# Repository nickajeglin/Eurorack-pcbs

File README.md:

# Eurorack-pcbs
A collection of easy to solder DIY eurorack PCB's. All IC's are SOIC or DIP, passives are 1206 or THT for ease of soldering. There are also faceplate drill templates and graphics that can be used for toner transfer. Some utility modules are set up as 1u pcb's so you can mix and match 3 at a time in a standard 3u panel with only 1 eurorack power connector needed. 

> [!IMPORTANT]
> # 2025 update
> I've been away from this for some time, but the modules are still good subject to the notes below. I've been trying to give away spare PCB's at events etc. If you have one of those please be sure to check the issues pages for some minor rework requirements depending on your PCB version. I don't have most socials, so if you need help you can try to dm me on reddit or maybe post an issue here. As a side note, I lost huge amount of data during a work move. That means anything mentioned below that isn't uploaded is gone :'( it's especially disappointing for the VCS, as it's one of my favorite modules. You can still find it with it's original designer [here.](https://github.com/kassu/kassutronics/tree/master/documentation/Slope)
> 
> I don't think that I will go back and recreate what is gone. Losing so much work is disappointing and disheartening, but truthfully it's time to move on. Back in 2019, unchecked mental illness helped me maintain the sort of work output that is unhealthy in the long run. As I've gotten a handle on that I've needed to slow down on some hobbies, and this is one of them.     
> This will probably be my last commit on this repository. I hope that these PCB's will help someone make some kickass music.
> 
> *Nick, 2025-01-03*
>
> **P.S.** One item thankfully spared from the data loss was my semi-artistic layout of the 1972 "surf synthesizer" detailed midway through [this article.](https://www.preservationsound.com/2011/01/music-synthesizers-in-popular-electronics-1972/) The original article is included in the build docs folder and has some tips on adjusting the circuit properly. Enjoy :D
> 
> 

# PCB status summary:
**VCA:** ready to build, digikey bom provided

**VCO:** ready to build, digikey bom provided, minor rework needed for V1.0, V2.0 ok. 

**Mult:** Super easy first DIY project no surface mount parts. Ready to build, see interactive BOM for parts list, there's only like 3.

**Mixer:**
Update 2019-04-28: prototypes built. I reversed the supply rails on the TL072 in the kicad schematic lol. That means I need to flip the power header, and change some silk around. Let me know if you want V1.0 and I'll email it to you

Update 2019-05-15: prototypes are working. I gotta put the revision together to fix the reversed supply issue, but my job is kicking my ass right now, so it could be a month or more before I get around to it. If you're desperate for a cheap mixer, shoot me an email and I'll send you V1 files. Rework of V1 consists of flipping the euro power header and bypass caps 180 deg from the silk on the PCB layout. 

**~1u LFO:** ready to build, minor rework needed for V1.0 !!There's a stalling issue at low frequency I can't figure out!! see the issues page for details You probably don't want to use this. I'm too dumb to figure out the stalling issue, so these are only good for 50hz-->audio rate modulation. I did a layout of David Haillant's LFO with SMD components, but I haven't asked permission to share the files yet. Watch this space. 

**3->1 averager/mixer:** Prototypes tested and working. Doing cleanup for release (bypass caps intefere with plugging the damn thing in). Let me know if you want V1.0 and I'll email it to you. 

**1u 1->3 mult:** ~~schematic finished, pcb layout in queue~~ I'll probably never get around to finishing this one, since I already did the BiggerBetter THT mult above. If you want a 1u mult bad let me know and I'll finish it up sometime while I'm supposed to be working :D. But really, if you want a 1u mult that bad you can probably figure it out yourself from muffwiggler forum posts. 

**VCF:** low priority for now--> maybe I'll make a tranisitor ladder VCF. 

**VCS:** PCB's are in, most of the pots are reversed as well as all of the SOT23 transistors. Otherwise it **kicks ass**. I haven't asked the kassutronics guy permission to post this one yet, but I'll get around to it once I've got a solid rework strategy for V1.0.

**LOGIC**: Ready to build. 

# General Notes

**How expensive is this?:** Common knowledge says that DIY is usually not cheaper than buying retail because economy of scale, educational mistakes etc. But look, eurorack modules are boutique shit, so in this case you'd be hard pressed to build this stuff for more than retail cost. Here's some fast numbers off the top of my head: BOM's for each module are between 20 and 50 USD with shipping. A run of 3-10 PCB's costs between 15 and 50 USD with shipping depending on fab house. So we'll call that 35-100 USD per module. If you're just starting out, plan to make lots of mistakes and double it. I've finished about 24 modules since January 2019 and spent about $1500 for an average of $62 per module. Now I have to sleep with one eye open so my wife doesn't kill me for life insurance money, but *learning is priceless* so at least there's that I guess.  

**IMPORTANT:** Do not plug these in backwards. First of all, (most) don't have any reverse polarity protection so it will probably kill the module. Second of all, I have no idea (and can't be responsible for) what will happen to the rest of the modules in your system if/when you do upend the power rails. Maybe I'll get around to adding rpp eventually, but for now I'm living dangerously by relying on shrouded headers. 

Most of these are not my circuit designs. I simply put them in kicad and did PCB layout for eurorack format. I'm a mechanical engineer, not an electrical one, so there may be minor (major lol) mistakes or violations of standard practice. I have tested all for functionality though. I can provide very limited support via email, but when it comes to troubleshooting, you're likely on your own. 

**SMD components**
All the passives on these are 1206 size components. As long as you have a [cheapo temperature controlled soldering iron](https://www.amazon.com/Weller-WLC100-40-Watt-Soldering-Station/dp/B000AS28UC/ref=sr_1_3?keywords=weller+soldering+station&qid=1558398140&s=hi&sr=1-3), it'll be no problem for you. After a little practice, you'll find them easier than through hole components. 

I know I said everything is 1206 size above, but I recently (04/2019) started using 0805 size parts. If you can handle 1206, I swear to god you can do 0805. They're basically the same width, so gripping them with tweezers is just as easy, but they're just a little shorter which makes laying out the PCB's much easier for me. Look at the ibom (interactive bom) files in each folder for the latest parts. I generate those straight from the latest PCB layouts before I upload, so they're guaranteed to have the correct part format. Mouser/digikey BOM's are more like 95% correct because I'm lazy. 

**Pots/Jacks/Switches**

Pots and jacks aren't included in any digikey or mouser carts. You want these ones if you're in the US: 

https://modularaddict.com/parts/synth-diy-parts/9mm-potentiometers

https://modularaddict.com/parts/jacks/pj301m12-jacks

Or similar from Thonk if you're in Europe. You can buy [several hundred jacks](https://www.aliexpress.com/item/Original-new-100-headset-socket-PJ-301M-3-5MM-audio-and-video-socket-measuring-90-degree/32919567094.html?spm=a2g0s.9042311.0.0.50554c4d2D22No) direct from China like I did, but you'll feel like a terrible person for not supporting your local diy suppliers, and the quality is *noticeably worse* than the ones from thonk or modular addict.    

Good switches can be hard to find. I love taiway switches from these people: 

https://lovemyswitches.com/categories/switches/toggle-switches/mini-toggle-switches.html

I have no affiliation with them, but they have switches with adorable little stubby levers, and I'll pay a premium for that shit any day. ~PCB's will accomodate "PCB mount" or "solder lug" style.~ Get PCB mount style for the moment. The current (2/2019) toggle switch footprint through holes are slightly narrow, so solder lug style switches require a little sand paper-ing of the terminals to fit.  

Faceplates: 2mm aluminum works perfectly. Regular drill bits will work, and you can cut it with woodworking tools if you're super careful. If you can't get ahold of that, go to a hobby or art store and get some 1/8" aircraft birch ply. It's thin but strong. I have been using toner transfer to print graphics and labelling onto the panels. It works for aluminum or wood and results in a distressed look that I kinda like. You can find a tutorial at instructables (https://www.instructables.com/id/Transfer-PHOTOS-to-METAL/) but here's the bullet points: 

1) Buy *water* based poly from the wood finish section of a hardware store. Paint a thin layer on the faceplate. 

2) Print out your design on a laser printer in reverse and stick it on the *wet* poly. 

3) Let it dry. I stick it in a warm oven to speed up the process.

4) Wet the paper, and gently rub it off. You don't need to get it all in 1 shot. You should repeat the drying and wetting/rubbing cycle 2 or 3 times to get the paper off without removing too much toner.

5) Hit it with another layer of poly for protection. 

**PCB fab houses**
I really like Aisler, but they are kind of expensive and shipping takes 2 weeks to the US (as of 5/2019 they now have US production, I haven't tried it yet though). They can definetly handle all of the features in these PCB's. I have also used oshpark with good results. JLCPCB is a cheaper option, even with 3 day DHL shipping to the US. All three can handle the plated slots for the jack and switch footprints with no problem.  

# Dual log/lin VCA: 

Design: Ray Wilson (please visit http://musicfromouterspace.com/)

Design alterations: None

Tested working 2019-02

Required kludges: The screw holes on the drill template are in a nonstandard spot. Adjust accordingly if you care

Notes: This one is super easy and goes together in less than an hour. It's a 2 board pannelized design. Make sure your PCB fab house can handle internal slots for the switch footprint and pannelization. (oshpark and aisler did it without issue.) I may revise this to a one board design in the future to reduce PCB costs. 

# VCO: 

Design: Ray Wilson (please visit http://musicfromouterspace.com/)

Design alterations: None

Tested working 2019-02

Required kludges: 

V2.0: Eurorack pwr connector interferes with pot feet on front of board. Simply bend one of the pot feet out of the way so it doesn't       contact the -12V side of the pwr connector. This is unlikely to be fixed in the near future unless someone else wants to reroute around a new power connector location. 

~V1.0 outer potentiometer leads for RV1 and RV2 are reversed and need to be jumpered (X style) to the correct holes.~

~Silk showing polarity for C12 is reversed (+ side of C12 should be at GND).~

~Eurorack pwr connector interferes with pot feet on front of board. Simply bend one of the pot feet out of the way so it doesn't       contact the -12V side of the pwr connector.~

Notes: U2 is really far away from U4. Use lots of flux and make sure that U1-U4 are soldered really nicely, otherwise it won't work. U5 has several pins that are not connected (specifically 2, 9, 10, 12, 15, 16). Depending on the PCB fab you use, they might instantly delaminate. Don't freak out, it's not a problem. There are some trimpot through holes that intersect jack footprints, so make sure you solder the jacks last, and clip the trimpot leads flush with the board.

# Mixer: 

Design: I guess this one is my own, but heavily influenced by information from Ray Wilson (please visit http://musicfromouterspace.com/)

Tested working 2019-02 (breadboard only)

Required kludges: N/A

Notes: PCB layout is incomplete as of 2019-02. This is a DC coupled (CV capable) 4 into 2 or 8 into 1 mixer. It's based off of Ray's mixers, but is simplified in that the switchable high gain channel has been replaced by a normal one. I have one of these running in my system right now that's just dead-bugged to the back of the faceplate. PCB layout is nearly completed, 

# Utility LFO (8K LFO)

(disregard the tht resistors, I ran out of smd ones, so I just bodged some on there.)

Design: Tim Parkhurst: Magic Smoke Electronics (http://electro-music.com/wiki/pmwiki.php?n=Schematics.MagicSmokeLFODesignByTimServo)

Design alterations: None

Tested working 2019-02

Required kludges: 
V2.0: Stalling may still be an issue at low freq. I'm working on that, see issue #14 if you can help. 

~V1.0:Coarse pot leads (RV11) are reversed. Swap them with jumpers. You also need to bend one of each pot support legs up under the pot to avoid the power chain pads. This circuit is stalling out at slow settings right now. See issue #14 if you can help explain why.~

Notes: This is shrunk down to be a 1u module. There are power chain jumpers so that you can put 3 of them in a standard 3u tall panel with only one eurorack pwr connector,  or you could build 1 and put it in a 1u tile. Pots are super close together, so the max knob size you can put on them is 13mm diameter. Davies 1900H clones from thonk or modular addict (or wherever) will be ok. 

# Buffered Mult

Design: Michael Barton (http://www.bartonmusicalcircuits.com) 

Design alterations: None

Tested working 2019-02

Required kludges: None

Notes: This one is actually THT. It's a super simple but emminently useful utility module. The only tip here is to make sure you place J10 and J13 before the power header if you use a shrouded connector. Otherwise the plastic shroud will cover up the tip connections. Provided with permission from Michael Barton. 
    
# Analog Logic

Design: ME!

tested working 2019-10-19

Notes: I'm excited about this one. It's my first real honest to god module design! 3 input attenuverting mixer that goes into analog AND, OR, an averager, and a comparator. You can use the attenuverters alone by plugging into the first row of jacks. This removes the corresponding signal from the logic section. Input 3 is normalled to +10V so it's attenuverter acts as the cutoff control if you don't plug anything into that jack.

NOTES FOR V1.0 PCB's: Prior to 2019-10-19. I mixed up diode footprints, so V1.0 boards have the miniscule SOD-523 footprint. V2.0 has SOD-323. Much more manageable.

V2.1 is current. I moved the potentiometers slightly based on feedback from a couple people. They're still on a diagonal, but a little further from the jacks and evenly spaced.

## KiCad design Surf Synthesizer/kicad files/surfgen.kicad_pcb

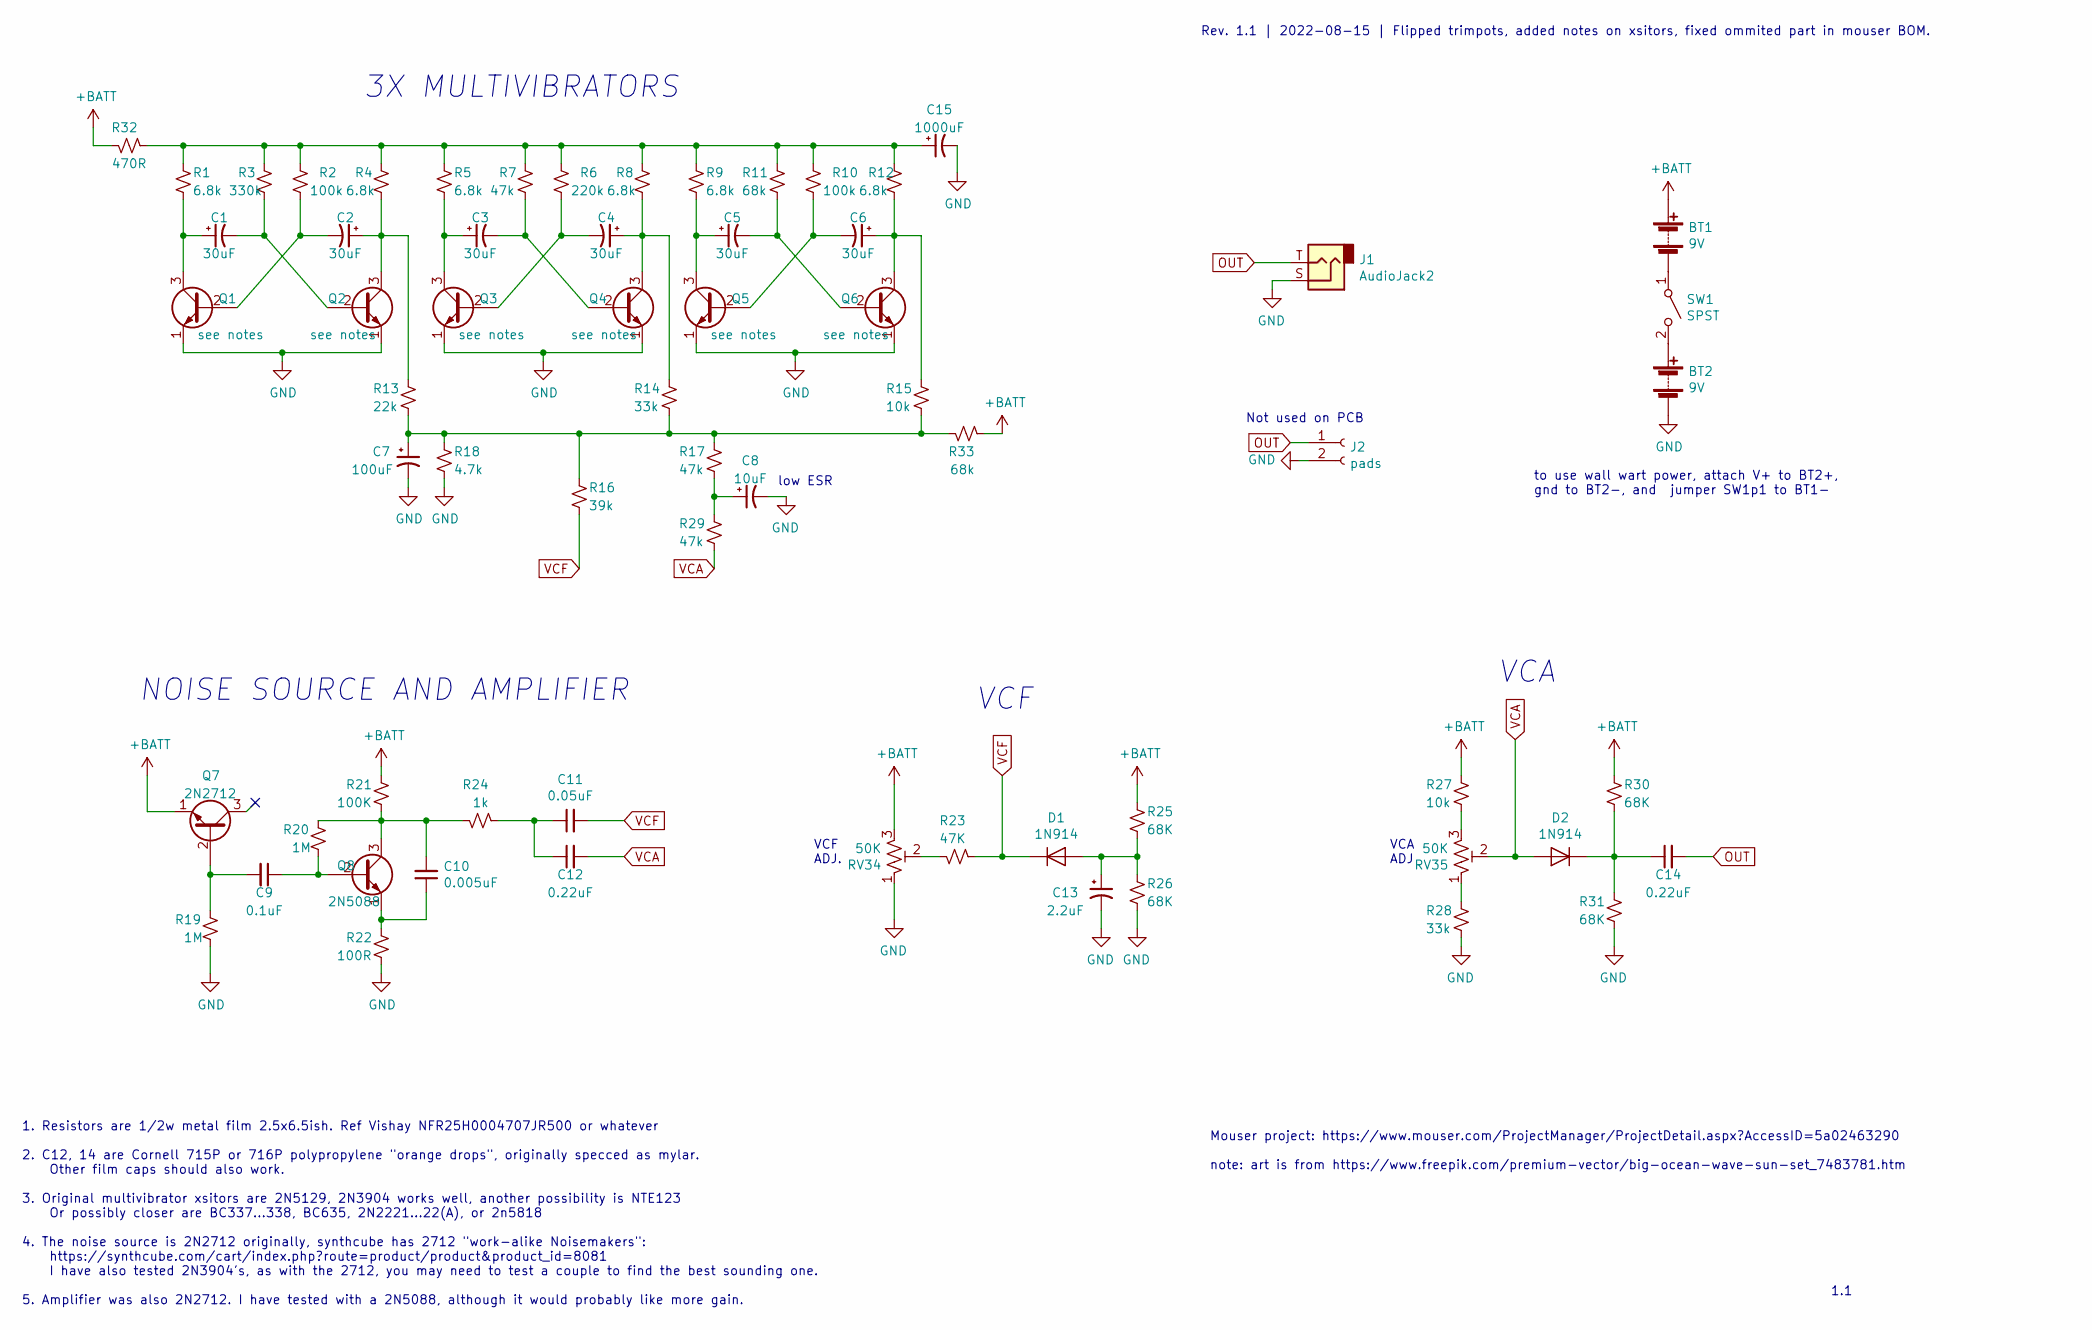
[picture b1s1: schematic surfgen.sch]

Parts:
BT1, BT2: 9V; TerminalBlock_Phoenix_MKDS-1,5-2-5.08_1x02_P5.08mm_Horizont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; Part Nr 651-1715721
C1, C2, C3, C4, C5, C6: 30uF; CP_Radial_D10.0mm_P5.00mm; Part Nr EGXF251ELL300MJ25S
C7: 100uF; CP_Radial_D10.0mm_P5.00mm; Part Nr MAL213631101E3
C8: 10uF; CP_Radial_D8.0mm_P5.00mm; Part Nr EEU-FR1H100B
C9: 0.1uF; C_Disc_D14.5mm_W5.0mm_P7.50mm; Part Nr S104Z93Z5VL83L0R
C10: 0.005uF; C_Disc_D11.0mm_W5.0mm_P7.50mm; Part Nr S502M39Z5UN63L6R
C11: 0.05uF; C_Disc_D16.0mm_W5.0mm_P10.00mm; Part Nr S503Z69Z5UL63L0R
C12, C14: 0.22uF; C_Rect_L28.0mm_W12.0mm_P22.50mm_MKS4; Part Nr 715P22452LD3
C13: 2.2uF; CP_Radial_D8.0mm_P5.00mm; Part Nr 860131274002
C15: 1000uF; C_Radial_D12.5mm_H20.0mm_P5.00mm; Part Nr EEU-FP1V102B
D1, D2: 1N914; D_DO-35_SOD27_P7.62mm_Horizontal; Part Nr 512-1N914
J1: AudioJack2; TerminalBlock_Phoenix_MKDS-1,5-2-5.08_1x02_P5.08mm_Horizont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; Part Nr 651-1715721
J2: pads; TerminalBlock_Phoenix_MKDS-1,5-2-5.08_1x02_P5.08mm_Horizont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; Part Nr 651-1715721
Q1, Q2, Q3, Q4, Q5, Q6: see notes; TO-92_HandSolder; Part Nr see notes
Q7: 2N2712; TO-92_HandSolder; Part Nr see notes
Q8: 2N5088; TO-92_HandSolder; Part Nr 610-2N5088
R1, R4, R5, R8, R9, R12: 6.8k; R_Axial_DIN0207_L6.3mm_D2.5mm_P10.16mm_Horizontal_refctr; Part Nr 71-CMF556K8000FKEB
R2, R10: 100k; R_Axial_DIN0207_L6.3mm_D2.5mm_P10.16mm_Horizontal_refctr; Part Nr 71-CMF55100K00BEEB
R3: 330k; R_Axial_DIN0207_L6.3mm_D2.5mm_P10.16mm_Horizontal_refctr; Part Nr 594-5053HD332K0F
R6: 220k; R_Axial_DIN0207_L6.3mm_D2.5mm_P10.16mm_Horizontal_refctr; Part Nr 71-CMF07220K00GKR6
R7, R17, R29: 47k; R_Axial_DIN0207_L6.3mm_D2.5mm_P10.16mm_Horizontal_refctr; Part Nr CMF5547K000FHEK
R11, R33: 68k; R_Axial_DIN0207_L6.3mm_D2.5mm_P10.16mm_Horizontal_refctr; Part Nr 594-SFR25H0006802JR5
R13: 22k; R_Axial_DIN0207_L6.3mm_D2.5mm_P10.16mm_Horizontal_refctr; Part Nr 594-5053HD22K10F
R14, R28: 33k; R_Axial_DIN0207_L6.3mm_D2.5mm_P10.16mm_Horizontal_refctr; Part Nr 594-SFR25H0003302JR5
R15, R27: 10k; R_Axial_DIN0207_L6.3mm_D2.5mm_P10.16mm_Horizontal_refctr; Part Nr 594-5053HD10K00F
R16: 39k; R_Axial_DIN0207_L6.3mm_D2.5mm_P10.16mm_Horizontal_refctr; Part Nr 594-5053HD39K20F
R18: 4.7k; R_Axial_DIN0207_L6.3mm_D2.5mm_P10.16mm_Horizontal_refctr; Part Nr 594-SFR25H0004701JR5
R19, R20: 1M; R_Axial_DIN0207_L6.3mm_D2.5mm_P10.16mm_Horizontal_refctr; Part Nr 594-SFR25H0001004JA5
R21: 100K; R_Axial_DIN0207_L6.3mm_D2.5mm_P10.16mm_Horizontal_refctr; Part Nr 71-CMF55100K00BEEB
R22: 100R; R_Axial_DIN0207_L6.3mm_D2.5mm_P10.16mm_Horizontal_refctr; Part Nr 594-5053HD100R0F
R23: 47K; R_Axial_DIN0207_L6.3mm_D2.5mm_P10.16mm_Horizontal_refctr; Part Nr CMF5547K000FHEK
R24: 1k; R_Axial_DIN0207_L6.3mm_D2.5mm_P10.16mm_Horizontal_refctr; Part Nr 594-5053HD1K000F
R25, R26, R30, R31: 68K; R_Axial_DIN0207_L6.3mm_D2.5mm_P10.16mm_Horizontal_refctr; Part Nr 594-SFR25H0006802JR5
R32: 470R; R_Axial_DIN0207_L6.3mm_D2.5mm_P10.16mm_Horizontal_refctr; Part Nr 594-SFR25H0004700FR5
RV34, RV35: 50K; Potentiometer_Bourns_3296Y_Vertical; Part Nr 3296Y-1-503LF
SW1: SPST; TerminalBlock_Phoenix_MKDS-1,5-2-5.08_1x02_P5.08mm_Horizont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; Part Nr 651-1715721

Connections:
+BATT: BT1.1 (+), Q7.1 (E), R21.1, R25.1, R27.1, R30.1, R32.1, R33.2, RV34.3
GND: BT2.2 (-), C7.2, C8.2, C13.2, C15.2, J1.S, J2.2, Q1.1 (E), Q2.1 (E), Q3.1 (E), Q4.1 (E), Q5.1 (E), Q6.1 (E), R18.2, R19.2, R22.2, R26.2, R28.2, R31.2, RV34.1
unnamed: BT1.2 (-), SW1.1 (A)
unnamed: BT2.1 (+), SW1.2 (B)
unnamed: C1.1, Q1.3 (C), R1.2
unnamed: C1.2, Q2.2 (B), R3.2
unnamed: C2.1, Q2.3 (C), R4.2, R13.1
unnamed: C2.2, Q1.2 (B), R2.2
unnamed: C3.1, Q3.3 (C), R5.2
unnamed: C3.2, Q4.2 (B), R7.2
unnamed: C4.1, Q4.3 (C), R8.2, R14.1
unnamed: C4.2, Q3.2 (B), R6.2
unnamed: C5.1, Q5.3 (C), R9.2
unnamed: C5.2, Q6.2 (B), R11.2
unnamed: C6.1, Q6.3 (C), R12.2, R15.1
unnamed: C6.2, Q5.2 (B), R10.2
unnamed: C7.1, R13.2, R14.2, R15.2, R16.1, R17.1, R18.1, R33.1
unnamed: C8.1, R17.2, R29.1
unnamed: C9.1, Q8.2 (B), R20.2
unnamed: C9.2, Q7.2 (B), R19.1
unnamed: C10.1, Q8.1 (E), R22.1
unnamed: C10.2, Q8.3 (C), R20.1, R21.2, R24.1
unnamed: C11.1, C12.1, R24.2
unnamed: C13.1, D1.2 (A), R25.2, R26.1
unnamed: C14.1, D2.1 (K), R30.2, R31.1
unnamed: C15.1, R1.1, R2.1, R3.1, R4.1, R5.1, R6.1, R7.1, R8.1, R9.1, R10.1, R11.1, R12.1, R32.2
unnamed: R23.1, RV34.2
unnamed: R27.2, RV35.3
unnamed: R28.1, RV35.1
OUT: C14.2, J1.T, J2.1
VCA: C12.2, D2.2 (A), R29.2, RV35.2
VCF: C11.2, D1.1 (K), R16.2, R23.2

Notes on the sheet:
3X MULTIVIBRATORS
NOISE SOURCE AND AMPLIFIER
VCF
VCA
low ESR
1. Resistors are 1/2w metal film 2.5x6.5ish. Ref Vishay NFR25H0004707JR500 or whatever 2. C12, 14 are Cornell 715P or 716P polypropylene "orange drops", originally specced as mylar. Other film caps should also work. 3. Original multivibrator xsitors are 2N5129, 2N3904 works well, another possibilit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
Mouser project: https://www.mouser.com/ProjectManager/ProjectDetail.aspx?AccessID=5a02463290 note: art is from https://www.freepik.com/premium-vector/big-ocean-wave-sun-set_7483781.htm
to use wall wart power, attach V+ to BT2+, gnd to BT2-, and jumper SW1p1 to BT1-
VCF ADJ.
VCA ADJ
Not used on PCB
Rev. 1.1 | 2022-08-15 | Flipped trimpots, added notes on xsitors, fixed ommited part in mouser BOM.
1.1

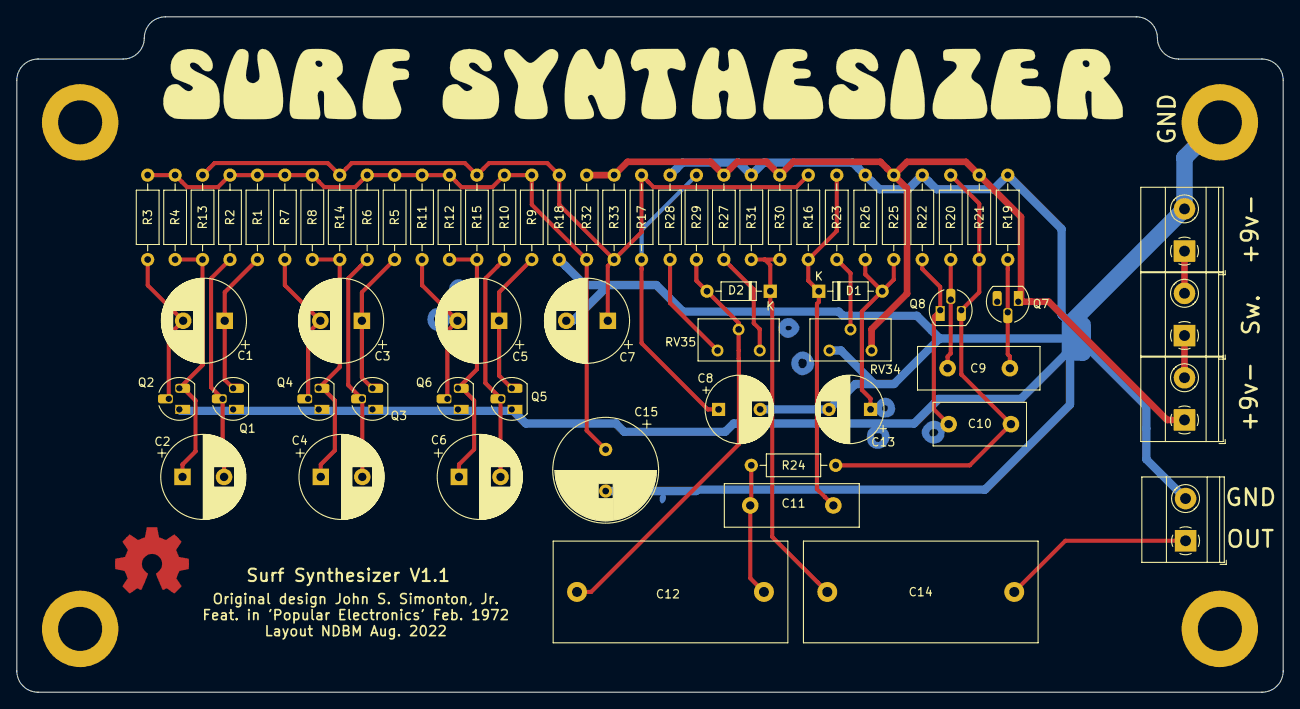
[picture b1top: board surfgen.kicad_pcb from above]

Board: 2 copper layers, 152.4 x 81.3 mm, 64 parts (0 on the bottom side), 32 nets.

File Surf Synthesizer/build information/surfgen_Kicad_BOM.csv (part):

"Source:","C:\Users\nick.bonnett-murphy\Documents\kicad\surfgen\surfgen.sch"
"Date:","8/2/2022 4:21:08 PM"
"Tool:","Eeschema (5.1.0)-1"
"Generator:","C:\Program Files\KiCad\bin\scripting\plugins/bom_csv_grouped_by_value.py"
"Component Count:","65"

"Individual Components:"

"Item","Qty","Reference(s)","Value","LibPart","Footprint","Datasheet","Part Nr"
"","","BT1","9V","Device:Battery","TerminalBlock_Phoenix:TerminalBlock_Phoenix_MKDS-1,5-2-5.08_1x02_P5.08mm_Horizontal","phoenix mkds series or compatible 5.08 pitch screw terminal","651-1715721"
"","","BT2","9V","Device:Battery","TerminalBlock_Phoenix:TerminalBlock_Phoenix_MKDS-1,5-2-5.08_1x02_P5.08mm_Horizontal","phoenix mkds series or compatible 5.08 pitch screw terminal","651-1715721"
"","","C1","30uF","Device:CP1_Small","Capacitor_THT:CP_Radial_D10.0mm_P5.00mm","~","EGXF251ELL300MJ25S"
"","","C2","30uF","Device:CP1_Small","Capacitor_THT:CP_Radial_D10.0mm_P5.00mm","~","EGXF251ELL300MJ25S"
"","","C3","30uF","Device:CP1_Small","Capacitor_THT:CP_Radial_D10.0mm_P5.00mm","~","EGXF251ELL300MJ25S"
"","","C4","30uF","Device:CP1_Small","Capacitor_THT:CP_Radial_D10.0mm_P5.00mm","~","EGXF251ELL300MJ25S"
"","","C5","30uF","Device:CP1_Small","Capacitor_THT:CP_Radial_D10.0mm_P5.00mm","~","EGXF251ELL300MJ25S"
"","","C6","30uF","Device:CP1_Small","Capacitor_THT:CP_Radial_D10.0mm_P5.00mm","~","EGXF251ELL300MJ25S"
"","","C7","100uF","Device:CP1_Small","Capacitor_THT:CP_Radial_D10.0mm_P5.00mm","~","MAL213631101E3 "
"","","C8","10uF","Device:CP1_Small","Capacitor_THT:CP_Radial_D8.0mm_P5.00mm","~","EEU-FR1H100B"
"","","C9","0.1uF","Device:C_Small","Capacitor_THT:C_Disc_D14.5mm_W5.0mm_P7.50mm","~","S104Z93Z5VL83L0R"
"","","C10","0.005uF","Device:C_Small","Capacitor_THT:C_Disc_D11.0mm_W5.0mm_P7.50mm","~","S502M39Z5UN63L6R"
"","","C11","0.05uF","Device:C_Small","Capacitor_THT:C_Disc_D16.0mm_W5.0mm_P10.00mm","~","S503Z69Z5UL63L0R "
"","","C12","0.22uF","Device:C_Small","Capacitor_THT:C_Rect_L28.0mm_W12.0mm_P22.50mm_MKS4","~","715P22452LD3"
"","","C13","2.2uF","Device:CP1_Small","Capacitor_THT:CP_Radial_D8.0mm_P5.00mm","~","860131274002 "
"","","C14","0.22uF","Device:C_Small","Capacitor_THT:C_Rect_L28.0mm_W12.0mm_P22.50mm_MKS4","~","715P22452LD3"
"","","C15","1000uF","Device:CP1_Small","Capacitor_THT:C_Radial_D12.5mm_H20.0mm_P5.00mm","~","EEU-FP1V102B"
"","","D1","1N914","Diode:1N914","Diode_THT:D_DO-35_SOD27_P7.62mm_Horizontal","http://www.vishay.com/docs/85622/1n914.pdf","512-1N914"
"","","D2","1N914","Diode:1N914","Diode_THT:D_DO-35_SOD27_P7.62mm_Horizontal","http://www.vishay.com/docs/85622/1n914.pdf","512-1N914"
"","","J1","AudioJack2","Connector:AudioJack2","TerminalBlock_Phoenix:TerminalBlock_Phoenix_MKDS-1,5-2-5.08_1x02_P5.08mm_Horizontal","phoenix mkds series or compatible 5.08 pitch screw terminal","651-1715721"
"","","J2","pads","Connector:Conn_01x02_Female","TerminalBlock_Phoenix:TerminalBlock_Phoenix_MKDS-1,5-2-5.08_1x02_P5.08mm_Horizontal","phoenix mkds series or compatible 5.08 pitch screw terminal","651-1715721"
"","","Q1","see schematic","Transistor_BJT:2N3904","Package_TO_SOT_THT:TO-92_HandSolder","https://www.fairchildsemi.com/datasheets/2N/2N3904.pdf","see schematic"
"","","Q2","see schematic","Transistor_BJT:2N3904","Package_TO_SOT_THT:TO-92_HandSolder","https://www.fairchildsemi.com/datasheets/2N/2N3904.pdf","see schematic"
"","","Q3","see schematic","Transistor_BJT:2N3904","Package_TO_SOT_THT:TO-92_HandSolder","https://www.fairchildsemi.com/datasheets/2N/2N3904.pdf","see schematic"
"","","Q4","see schematic","Transistor_BJT:2N3904","Package_TO_SOT_THT:TO-92_HandSolder","https://www.fairchildsemi.com/datasheets/2N/2N3904.pdf","see schematic"
"","","Q5","see schematic","Transistor_BJT:2N3904","Package_TO_SOT_THT:TO-92_HandSolder","https://www.fairchildsemi.com/datasheets/2N/2N3904.pdf","see schematic"
"","","Q6","see schematic","Transistor_BJT:2N3904","Package_TO_SOT_THT:TO-92_HandSolder","https://www.fairchildsemi.com/datasheets/2N/2N3904.pdf","see schematic"
"","","Q7","2N2712","Transistor_BJT:2N3904","Package_TO_SOT_THT:TO-92_HandSolder","https://www.fairchildsemi.com/datasheets/2N/2N3904.pdf","see schematic"
"","","Q8","2N5088","Transistor_BJT:2N3904","Package_TO_SOT_THT:TO-92_HandSolder","https://www.fairchildsemi.com/datasheets/2N/2N3904.pdf","610-2N5088"
"","","R1","6.8k","Device:R_Small_US","custom parts:R_Axial_DIN0207_L6.3mm_D2.5mm_P10.16mm_Horizontal_refctr","~","71-CMF556K8000FKEB"
"","","R2","100k","Device:R_Small_US","custom parts:R_Axial_DIN0207_L6.3mm_D2.5mm_P10.16mm_Horizontal_refctr","~","71-CMF55100K00BEEB"
"","","R3","330k","Device:R_Small_US","custom parts:R_Axial_DIN0207_L6.3mm_D2.5mm_P10.16mm_Horizontal_refctr","~","594-5053HD332K0F"
"","","R4","6.8k","Device:R_Small_US","custom parts:R_Axial_DIN0207_L6.3mm_D2.5mm_P10.16mm_Horizontal_refctr","~","71-CMF556K8000FKEB"
"","","R5","6.8k","Device:R_Small_US","custom parts:R_Axial_DIN0207_L6.3mm_D2.5mm_P10.16mm_Horizontal_refctr","~","71-CMF556K8000FKEB"
"","","R6","220k","Device:R_Small_US","custom parts:R_Axial_DIN0207_L6.3mm_D2.5mm_P10.16mm_Horizontal_refctr","~","71-CMF07220K00GKR6"
"","","R7","47k","Device:R_Small_US","custom parts:R_Axial_DIN0207_L6.3mm_D2.5mm_P10.16mm_Horizontal_refctr","~","CMF5547K000FHEK"
"","","R8","6.8k","Device:R_Small_US","custom parts:R_Axial_DIN0207_L6.3mm_D2.5mm_P10.16mm_Horizontal_refctr","~","71-CMF556K8000FKEB"
"","","R9","6.8k","Device:R_Small_US","custom parts:R_Axial_DIN0207_L6.3mm_D2.5mm_P10.16mm_Horizontal_refctr","~","71-CMF556K8000FKEB"
"","","R10","100k","Device:R_Small_US","custom parts:R_Axial_DIN0207_L6.3mm_D2.5mm_P10.16mm_Horizontal_refctr","~","71-CMF55100K00BEEB"
"","","R11","68k","Device:R_Small_US","custom parts:R_Axial_DIN0207_L6.3mm_D2.5mm_P10.16mm_Horizontal_refctr","~","594-SFR25H0006802JR5"
"","","R12","6.8k","Device:R_Small_US","custom parts:R_Axial_DIN0207_L6.3mm_D2.5mm_P10.16mm_Horizontal_refctr","~","71-CMF556K8000FKEB"
"","","R13","22k","Device:R_Small_US","custom parts:R_Axial_DIN0207_L6.3mm_D2.5mm_P10.16mm_Horizontal_refctr","~","594-5053HD22K10F"
"","","R14","33k","Device:R_Small_US","custom parts:R_Axial_DIN0207_L6.3mm_D2.5mm_P10.16mm_Horizontal_refctr","~","594-SFR25H0003302JR5"
"","","R15","10k","Device:R_Small_US","custom parts:R_Axial_DIN0207_L6.3mm_D2.5mm_P10.16mm_Horizontal_refctr","~","594-5053HD10K00F"
"","","R16","39k","Device:R_Small_US","custom parts:R_Axial_DIN0207_L6.3mm_D2.5mm_P10.16mm_Horizontal_refctr","~","594-5053HD39K20F"
"","","R17","47k","Device:R_Small_US","custom parts:R_Axial_DIN0207_L6.3mm_D2.5mm_P10.16mm_Horizontal_refctr","~","CMF5547K000FHEK"
"","","R18","4.7k","Device:R_Small_US","custom parts:R_Axial_DIN0207_L6.3mm_D2.5mm_P10.16mm_Horizontal_refctr","~","594-SFR25H0004701JR5"
"","","R19","1M","Device:R_Small_US","custom parts:R_Axial_DIN0207_L6.3mm_D2.5mm_P10.16mm_Horizontal_refctr","~","594-SFR25H0001004JA5"
"","","R20","1M","Device:R_Small_US","custom parts:R_Axial_DIN0207_L6.3mm_D2.5mm_P10.16mm_Horizontal_refctr","~","594-SFR25H0001004JA5"
"","","R21","100K","Device:R_Small_US","custom parts:R_Axial_DIN0207_L6.3mm_D2.5mm_P10.16mm_Horizontal_refctr","~","71-CMF55100K00BEEB"
"","","R22","100R","Device:R_Small_US","custom parts:R_Axial_DIN0207_L6.3mm_D2.5mm_P10.16mm_Horizontal_refctr","~","594-5053HD100R0F"
"","","R23","47K","Device:R_Small_US","custom parts:R_Axial_DIN0207_L6.3mm_D2.5mm_P10.16mm_Horizontal_refctr","~","CMF5547K000FHEK"
"","","R24","1k","Device:R_Small_US","custom parts:R_Axial_DIN0207_L6.3mm_D2.5mm_P10.16mm_Horizontal_refctr","~","594-5053HD1K000F"
"","","R25","68K","Device:R_Small_US","custom parts:R_Axial_DIN0207_L6.3mm_D2.5mm_P10.16mm_Horizontal_refctr","~","594-SFR25H0006802JR5"
"","","R26","68K","Device:R_Small_US","custom parts:R_Axial_DIN0207_L6.3mm_D2.5mm_P10.16mm_Horizontal_refctr","~","594-SFR25H0006802JR5"
"","","R27","10k","Device:R_Small_US","custom parts:R_Axial_DIN0207_L6.3mm_D2.5mm_P10.16mm_Horizontal_refctr","~","594-5053HD10K00F"
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
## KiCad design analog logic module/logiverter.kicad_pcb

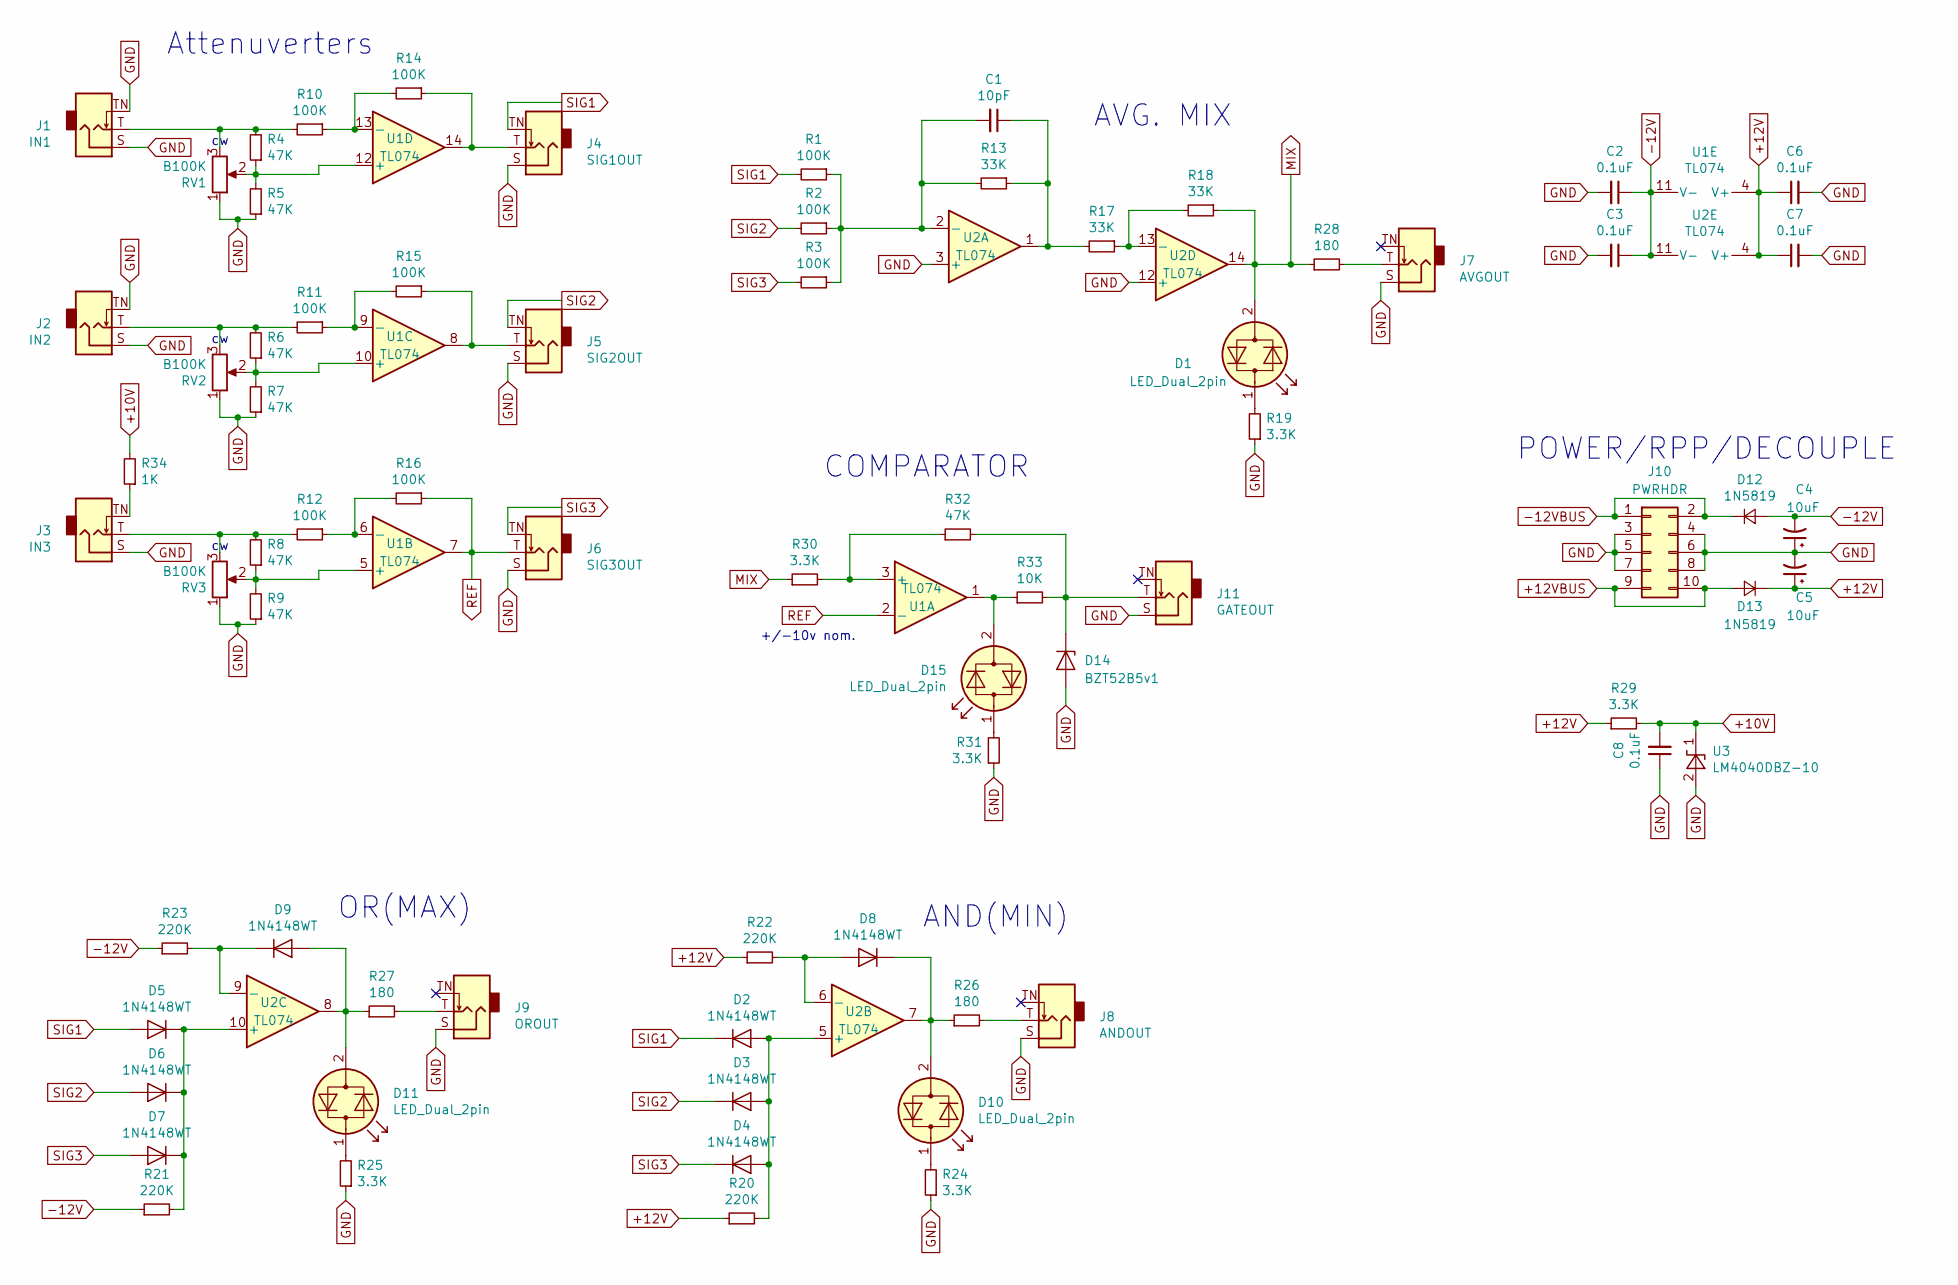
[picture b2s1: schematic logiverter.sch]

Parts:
C1: 10pF; C_0805_2012Metric_Pad1.15x1.40mm_HandSolder
C2, C3, C6, C7, C8: 0.1uF; C_0805_2012Metric_Pad1.15x1.40mm_HandSolder
C4, C5: 10uF; CP_Elec_5x5.4
D1, D10, D11, D15: LED_Dual_2pin; LED_D3.0mm
D2, D3, D4, D5, D6, D7, D8, D9: 1N4148WT; D_SOD-523
D12, D13: 1N5819; D_SOD-123
D14: BZT52B5v1; D_SOD-123
J1: IN1; 3.5mm_tip_switch_thonkiconn
J2: IN2; 3.5mm_tip_switch_thonkiconn
J3: IN3; 3.5mm_tip_switch_thonkiconn
J4: SIG1OUT; 3.5mm_tip_switch_thonkiconn
J5: SIG2OUT; 3.5mm_tip_switch_thonkiconn
J6: SIG3OUT; 3.5mm_tip_switch_thonkiconn
J7: AVGOUT; 3.5mm_tip_switch_thonkiconn
J8: ANDOUT; 3.5mm_tip_switch_thonkiconn
J9: OROUT; 3.5mm_tip_switch_thonkiconn
J10: PWRHDR; IDC-Header_2x05_P2.54mm_Vertical
J11: GATEOUT; 3.5mm_tip_switch_thonkiconn
R1, R2, R3, R10, R11, R12, R14, R15, R16: 100K; R_0805_2012Metric_Pad1.15x1.40mm_HandSolder
R4, R5, R6, R7, R8, R9, R32: 47K; R_0805_2012Metric_Pad1.15x1.40mm_HandSolder
R13, R17, R18: 33K; R_0805_2012Metric_Pad1.15x1.40mm_HandSolder
R19, R24, R25, R29, R30, R31: 3.3K; R_0805_2012Metric_Pad1.15x1.40mm_HandSolder
R20, R21, R22, R23: 220K; R_0805_2012Metric_Pad1.15x1.40mm_HandSolder
R26, R27, R28: 180; R_0805_2012Metric_Pad1.15x1.40mm_HandSolder
R33: 10K; R_0805_2012Metric_Pad1.15x1.40mm_HandSolder
R34: 1K; R_0805_2012Metric_Pad1.15x1.40mm_HandSolder
RV1, RV2, RV3: B100K; Potentiometer_Vertical_Bournes_PTV09A
U1, U2: TL074; SOIC-14_3.9x8.7mm_P1.27mm
U3: LM4040DBZ-10; SOT-23_Handsoldering

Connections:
+10V: C8.2, R29.2, R34.2, U3.1 (K)
+12V: C5.1, C6.1, C7.1, D13.1 (K), R20.1, R22.1, R29.1, U1.4 (V+), U2.4 (V+)
+12VBUS: D13.2 (A), J10.9, J10.10
-12V: C2.1, C3.1, C4.2, D12.2 (A), R21.1, R23.1, U1.11 (V-), U2.11 (V-)
-12VBUS: D12.1 (K), J10.1, J10.2
GND: C2.2, C3.2, C4.1, C5.2, C6.2, C7.2, C8.1, D14.2 (A), J1.S, J1.TN, J2.S, J2.TN, J3.S, J4.S, J5.S, J6.S, J7.S, J8.S, J9.S, J10.3, J10.4, J10.5, J10.6, J10.7, J10.8, J11.S, R5.1, R7.1, R9.1, R19.1, R24.1, R25.1, R31.1, RV1.1, RV2.1, RV3.1, U2.3 (+), U2.12 (+), U3.2 (A)
MIX: D1.2 (AK), R18.1, R28.1, R30.1, U2.14
unnamed: C1.1, R13.1, R17.2, U2.1
unnamed: C1.2, R1.1, R2.1, R3.1, R13.2, U2.2 (-)
unnamed: D1.1 (KA), R19.2
unnamed: D2.2 (A), D3.2 (A), D4.2 (A), R20.2, U2.5 (+)
unnamed: D5.1 (K), D6.1 (K), D7.1 (K), R21.2, U2.10 (+)
unnamed: D8.2 (A), R22.2, U2.6 (-)
unnamed: D9.1 (K), R23.2, U2.9 (-)
unnamed: D10.1 (KA), R24.2
unnamed: D8.1 (K), D10.2 (AK), R26.1, U2.7
unnamed: D11.1 (KA), R25.2
unnamed: D9.2 (A), D11.2 (AK), R27.1, U2.8
unnamed: D14.1 (K), J11.T, R32.2, R33.2
unnamed: D15.1 (KA), R31.2
unnamed: D15.2 (AK), R33.1, U1.1
unnamed: J1.T, R4.2, R10.2, RV1.3
unnamed: J2.T, R6.2, R11.2, RV2.3
unnamed: J3.T, R8.2, R12.2, RV3.3
unnamed: J3.TN, R34.1
unnamed: J4.T, R14.1, U1.14
unnamed: J5.T, R15.1, U1.8
unnamed: J7.T, R28.2
unnamed: J8.T, R26.2
unnamed: J9.T, R27.2
unnamed: R4.1, R5.2, RV1.2, U1.12 (+)
unnamed: R6.1, R7.2, RV2.2, U1.10 (+)
unnamed: R8.1, R9.2, RV3.2, U1.5 (+)
unnamed: R10.1, R14.2, U1.13 (-)
unnamed: R11.1, R15.2, U1.9 (-)
unnamed: R12.1, R16.2, U1.6 (-)
unnamed: R17.1, R18.2, U2.13 (-)
unnamed: R30.2, R32.1, U1.3 (+)
REF: J6.T, R16.1, U1.2 (-), U1.7
SIG1: D2.1 (K), D5.2 (A), J4.TN, R1.2
SIG2: D3.1 (K), D6.2 (A), J5.TN, R2.2
SIG3: D4.1 (K), D7.2 (A), J6.TN, R3.2

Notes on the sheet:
Attenuverters
OR(MAX)
AND(MIN)
AVG. MIX
POWER/RPP/DECOUPLE
COMPARATOR
+/-10v nom.

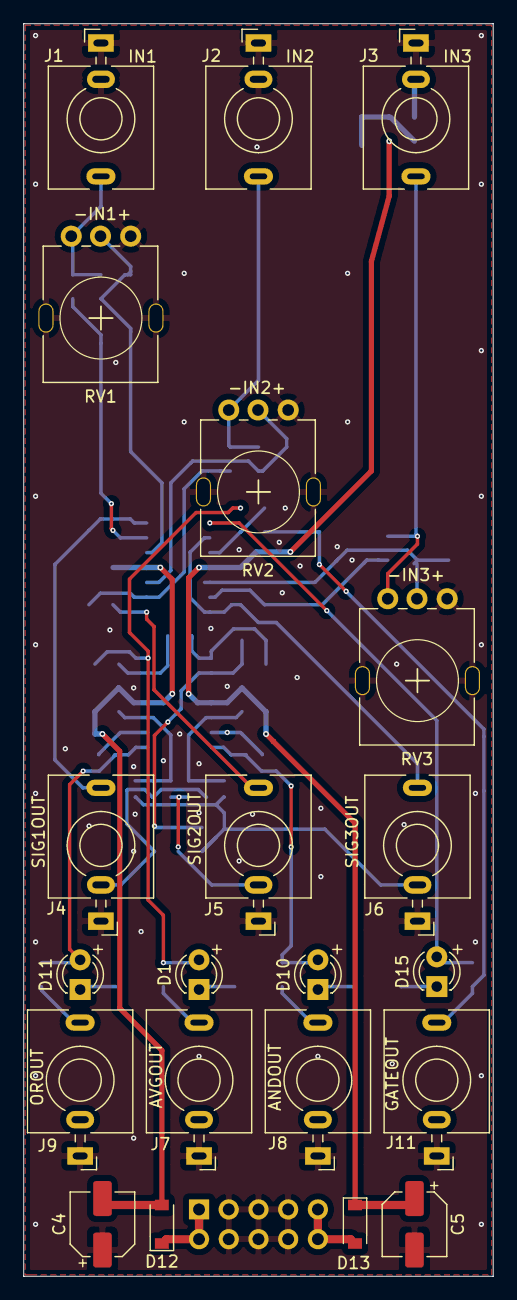
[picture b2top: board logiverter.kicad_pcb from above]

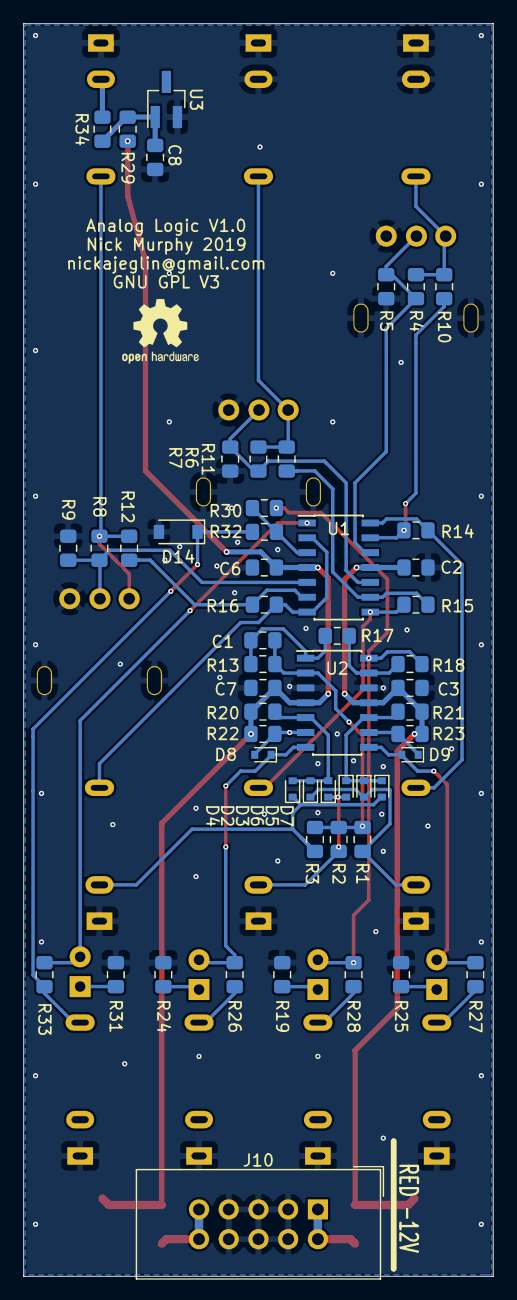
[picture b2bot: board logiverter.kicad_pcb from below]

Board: 2 copper layers, 40.1 x 107.1 mm, 74 parts (53 on the bottom side), 42 nets.

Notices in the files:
Buf. Mult/mult.kicad_pcb:
CC-BY-SA
analog logic module/logiverter.kicad_pcb:
GNU GPL V3
